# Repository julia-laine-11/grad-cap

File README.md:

# grad-cap
This is a pcb for my grad cap

## Physical:
- the pcb should cover the whole cap
- the pcb should have a space for the little tassle knob in the middle
- the battery should be flat and fit underneath the cap or pcb
- the fireworks should move while the power is on

### LED Sequence:

This was previously 16 frames, but I reduced it to 8 due to the crazy amount of traces needed (and the large amount of time to animate it). I also limited each LED to 2 frames at maximum and reduced the amount of LEDs per firework.
8 frames should be easier to route and less expensive for me to manufacture, lol

### Hardware
- While I originally planned to use a 555 timer, the MIP557 is made to be used in astable mode so I will use that
- It will have a potentiometer instead of a static resistor so that the frame rate can be sped up/lowered

- I did add a footprint for a 555 on the back in case I cannot get this chip to work. I do not have one in person to prototype with.

- the pulse will go into a binary incrementer. At first I was going to use make it myself with 3 flip flops but I couldn't find the chips I needed at the ECE shop so I will just use a binary incrementer that is available.

- the output of the incrementer is then demuxed 3:8

- the demuxed output then goes to OR gates for sections that are active for multiple frames

- and then the rest of the outputs from the mux and the outputs from the OR gates are sent to the MOSFETs

- the LEDs are color coded to what section they are a part of.
- from vote of my friends and family, the stems of the fireworks are white while the blooms are different color.

LED resistors:
- input: 3.7v  

  - white: 3.1v  20mA
  
    - 3.7-3.1 = .6/.02 = 30

  - amber: 2v 20mA
  
    - 3.7-2 = 1.7/.02 = 85

  - red: 2v 20mA
  
    - 3.7-2 = 1.7/.02 = 85

  - green: 2.2v 20mA
  
    - 3.7-2.2 = 1.5/.02 = 75
   
30 ohms: 16

80 ohms: 51

#### Prototyping
- I used the 3v output from my STM proto board to power it. The battery will output 3.7v but all of the datasheets say the components can use 3.7v so it's fine.
- I was having difficulty with the output (the gif is short, but yes this is the output)

- This was frustrating since the outputs from the incrementor were displaying properly. (from top to bottom- clock, A0, A1, A2)

- turns out I had the outputs mismatched. I had the input to the mux (A1 and A0) swapped.

- here it is working (going counting in order - 1 is at the top)

- I also needed to check my sizing now that I actually have my cap. I got the initial measurements from a friend who already graduated

- Square width: 23.5 cm
- Button diameter: 2.36 cm

    - I will make the overall board a little less than the square width, and the hole for the button a little larger.

- initial kicad measurements from my friend:

- Rectangle: 24cm, button: 26cm
- rectangle needs to shrink, button is fine :)

- final shape:

#### PCB Images 😀
- I am still working on the silkscreen

- the purdue emblem is on the solder mask layer so it is copper colored
- the handwriting is in silkscreen

- The trace widths for the main branches are 22mils. there are a maximum of ~8 LEDs per branch so I used the digikey trace width calculator and found this width is fine. there are no internal layers so I didnt need to make it any wider.
- power traces are 40 mils.

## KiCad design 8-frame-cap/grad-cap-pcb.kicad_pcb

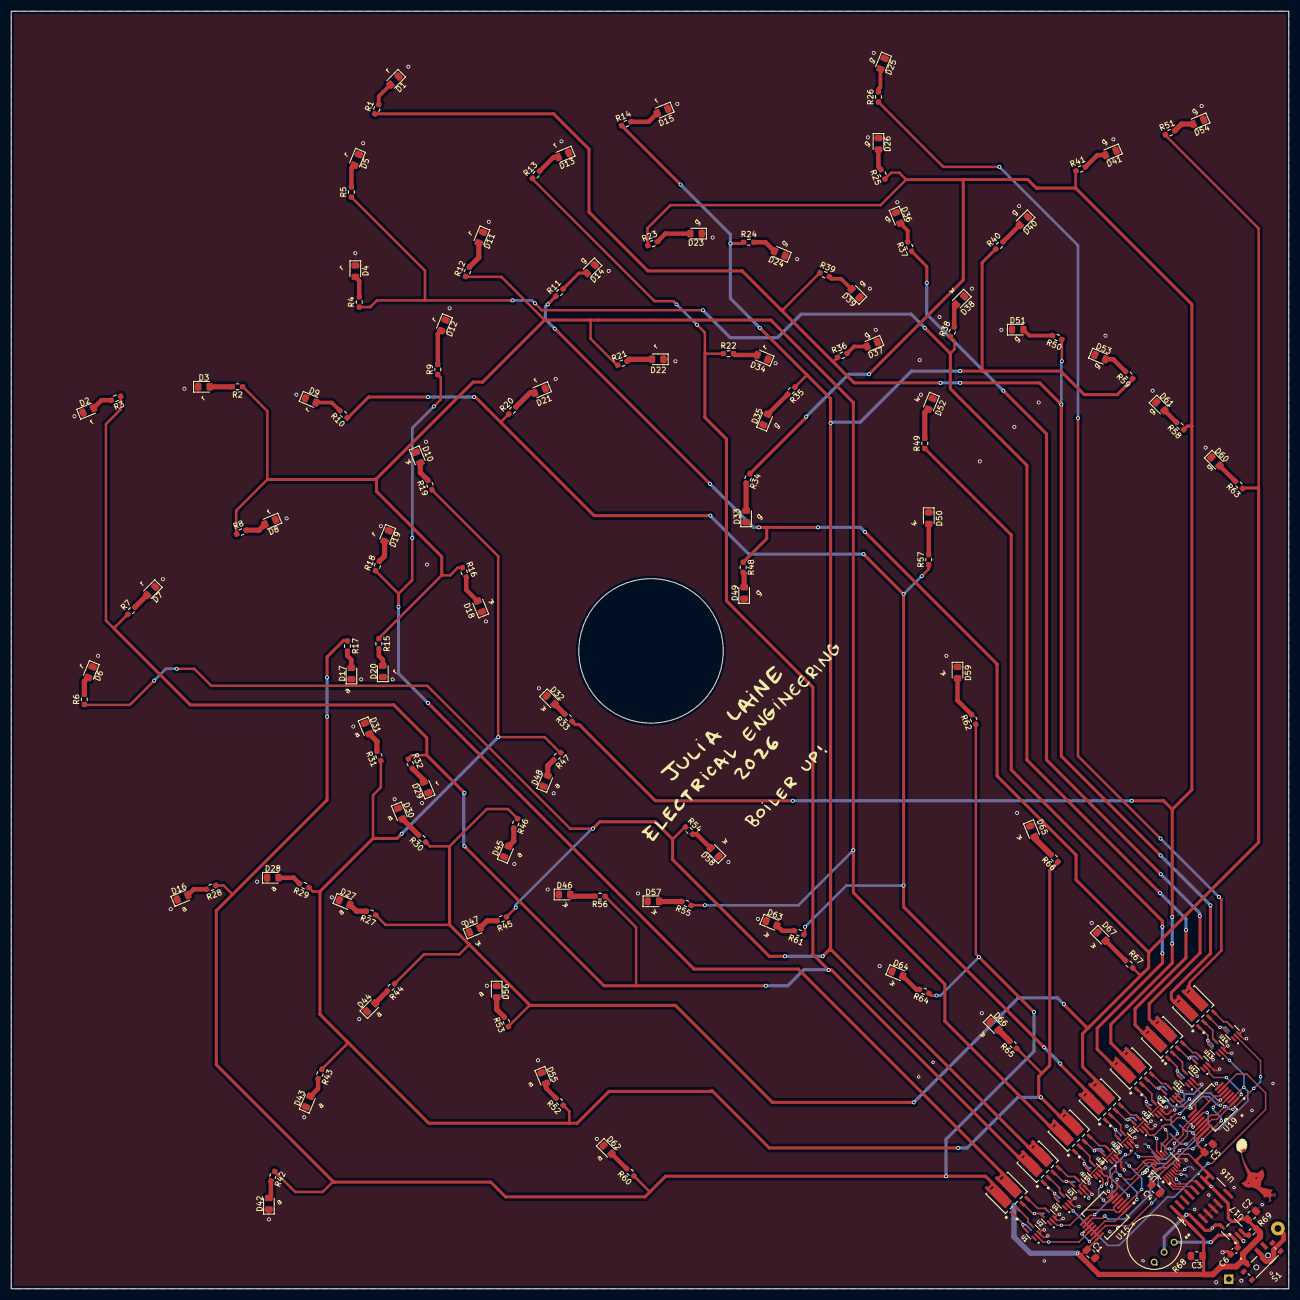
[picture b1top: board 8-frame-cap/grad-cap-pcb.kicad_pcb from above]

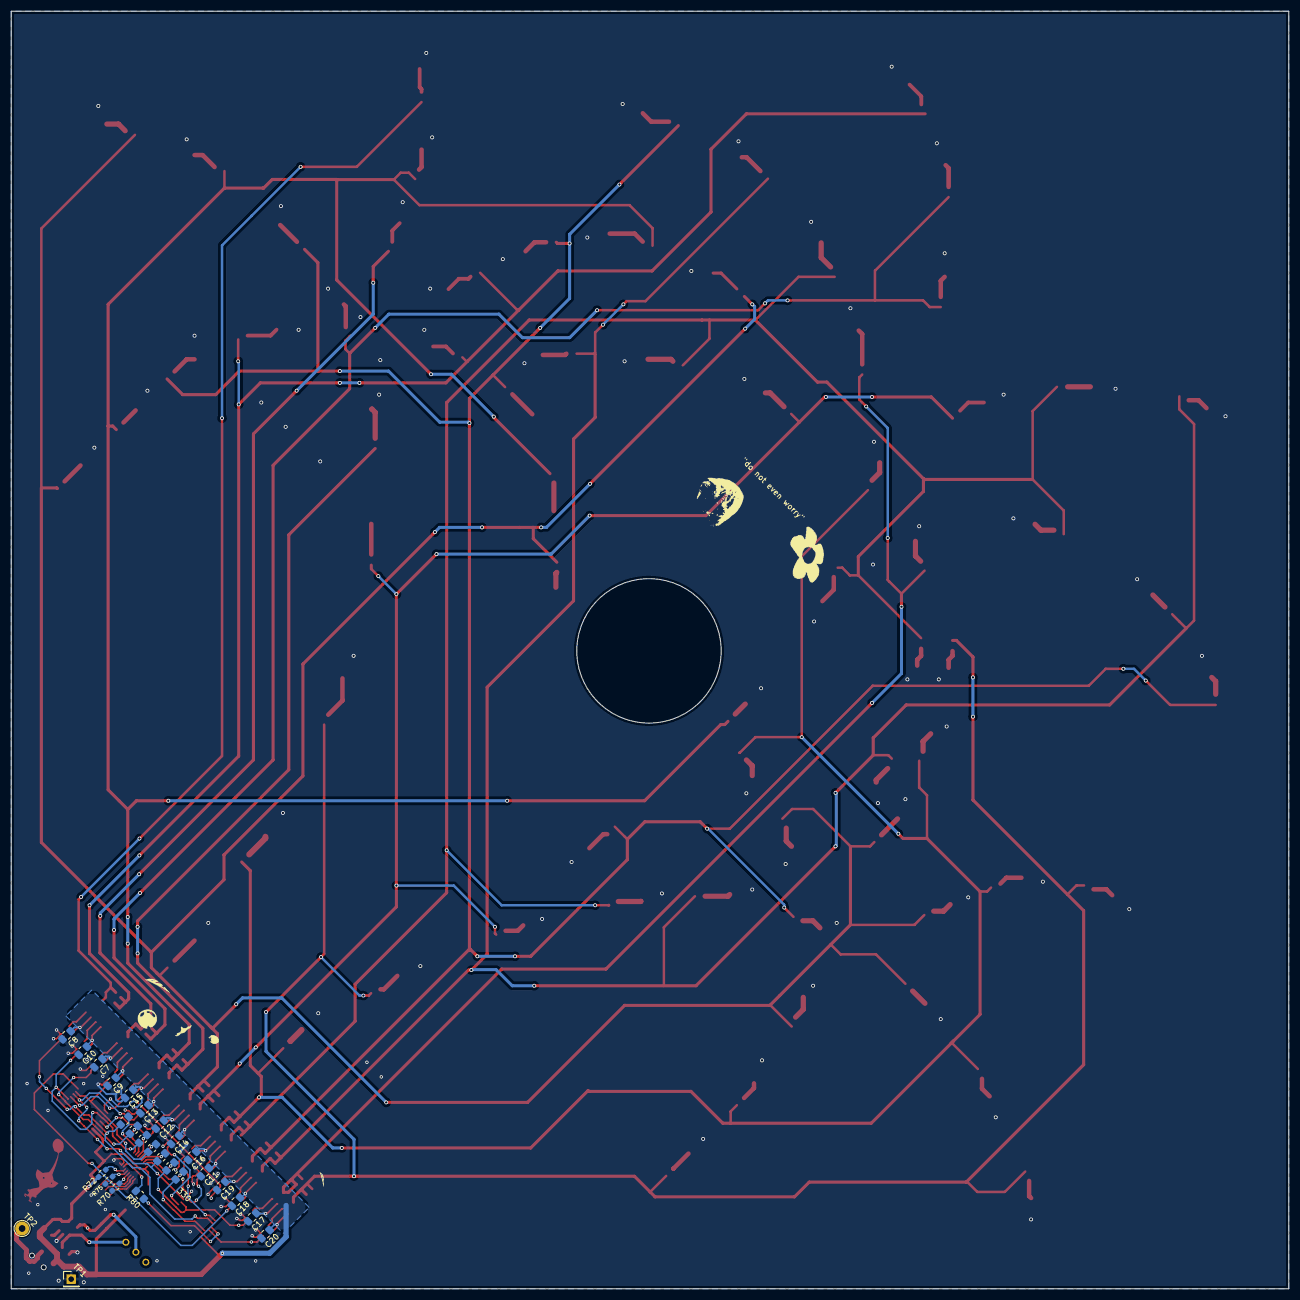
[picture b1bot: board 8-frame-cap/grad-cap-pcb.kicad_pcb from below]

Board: 2 copper layers, 230.0 x 230.0 mm, 196 parts (27 on the bottom side), 131 nets.

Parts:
C1, C2, C3, C4, C5, C7, C8, C9, C10, C11, C12, C13, C14, C15, C16, C17, C18, C19, C20: .1uf; C_0805_2012Metric_Pad1.18x1.45mm_HandSolder
C6: .1uF; C_0603_1608Metric_Pad1.08x0.95mm_HandSolder
D1, D2, D3, D4, D5, D6, D7, D8, D9, D10, D11, D12, D13, D14, D15, D16, D17, D18, D19, D20, D21, D22, D23, D24, D25, D26, D27, D28, D29, D30, D31, D32, D33, D34, D35, D36, D37, D38, D39, D40, D41, D42, D43, D44, D45, D46, D47, D48, D49, D50, D51, D52, D53, D54, D55, D56, D57, D58, D59, D60, D61, D62, D63, D64, D65, D66, D67: LED_0805_2012Metric_Pad1.15x1.40mm_HandSolder
R1, R2, R3, R4, R5, R6, R7, R8, R9, R10, R11, R12, R13, R14, R15, R16, R17, R18, R19, R20, R21, R22, R23, R24, R25, R26, R27, R28, R29, R30, R31, R32, R33, R34, R35, R36, R37, R38, R39, R40, R41, R42, R43, R44, R45, R46, R47, R48, R49, R50, R51, R52, R53, R54, R55, R56, R57, R58, R59, R60, R61, R62, R63, R64, R65, R66, R67: R_Small_US; R_0603_1608Metric_Pad0.98x0.95mm_HandSolder
R68: 91AR1MEGLF; 1M-potentiometer
R69: 1M; R_0603_1608Metric_Pad0.98x0.95mm_HandSolder
R70, R72, R75: 10k; R_0603_1608Metric_Pad0.98x0.95mm_HandSolder
R71, R73, R74, R76, R77, R78, R79, R80: 300; R_0805_2012Metric_Pad1.20x1.40mm_HandSolder
S1: ON/OFF; spdt-switch
T1, T2, T3, T4, T5, T6, T7: PHPT610035PKX; PHPT610035PKX_TRANS-2PNP-100V-3A
TP1: TestPoint; PinHeader_1x01_P2.54mm_Vertical
TP2: TestPoint; TestPoint_THTPad_D2.5mm_Drill1.2mm
U1, U2, U3, U4, U5, U6, U7, U8, U9, U10, U11, U12, U13, U14: SN74LVC1G14DCKR; SN74LVC-INVERTER
U15, U19: SN74AHCT32DBR; SN74AHCT32DBR_2-INPUT-QUAD-OR
U16: SN74HC163DR; binary counter - 74hc163
U17: MIC1557YM5-TR; MIC1557
U18: SN74HCS238DYYR; SN74HCS238DYYR-3-8-MUX

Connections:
0: R78.2, U15.1 (1A), U15.12 (4A)
1: R73.2, U2.2 (A), U15.2 (1B), U15.4 (2A)
1or2: R10.1, R20.1, R57.1, R61.1, T5.8 (COLLECTOR)
2: R74.2, U5.2 (A), U15.5 (2B), U19.4 (2A)
2or3: R2.1, R8.1, R12.1, R15.1, R16.1, R21.1, R55.1, T3.8 (COLLECTOR)
3: R79.2, U11.2 (A), U19.5 (2B), U19.9 (3A)
3or4: R3.1, R7.1, R13.1, R22.1, R32.1, R56.1, T2.8 (COLLECTOR)
4: R77.2, U13.2 (A), U19.2 (1B), U19.10 (3B)
4or5: R6.1, R14.1, R24.1, R35.1, R40.1, R45.1, R54.1, R59.1, T2.6 (COLLECTOR)
5: R76.2, U12.2 (A), U19.1 (1A), U19.13 (4B)
5or6: R23.1, R25.1, R33.1, R34.1, R41.1, R58.1, T4.6 (COLLECTOR)
6: R71.2, U14.2 (A), U15.9 (3A), U19.12 (4A)
6or7: R11.1, R27.1, R30.1, R44.1, R46.1, R48.1, R51.1, R53.1, R63.1, R67.1, T5.6 (COLLECTOR)
7: R80.1, U15.10 (3B), U15.13 (4B)
7or8: R19.1, R29.1, R31.1, R43.1, R47.1, R52.1, R65.1, R66.1, T3.6 (COLLECTOR)
8or1: R17.1, R28.1, R42.1, R60.1, R62.1, R64.1, T1.8 (COLLECTOR)
557-PULSE: R68.2, U16.2 (CLK), U17.5 (OUT)
+3.3V: C1.1, C2.1, C3.1, C4.1, C5.1, C7.1, C8.1, C9.1, C10.1, C11.1, C12.1, C13.1, C14.1, C15.1, C16.1, C17.1, C18.1, C19.1, C20.1, R69.1, R72.2, S1.1, T1.1 (EMITTER), T1.3 (EMITTER), T2.1 (EMITTER), T2.3 (EMITTER), T3.1 (EMITTER), T3.3 (EMITTER), T4.1 (EMITTER), T4.3 (EMITTER), T5.1 (EMITTER), T5.3 (EMITTER), T6.1 (EMITTER), T6.3 (EMITTER), T7.1 (EMITTER), T7.3 (EMITTER), U1.5 (VCC), U2.5 (VCC), U3.5 (VCC), U4.5 (VCC), U5.5 (VCC), U6.5 (VCC), U7.5 (VCC), U8.5 (VCC), U9.5 (VCC), U10.5 (VCC), U11.5 (VCC), U12.5 (VCC), U13.5 (VCC), U14.5 (VCC), U15.14 (VCC), U16.1 (*CLR), U16.7 (ENP), U16.9 (*LOAD), U16.10 (ENT), U16.16 (VCC), U17.4 (VS), U18.16 (VCC), U19.14 (VCC)
+BATT: S1.2, TP2.1
/pd-mux-g0: R70.1, U18.4 (*G0)
/pd-mux-g1: R75.1, U18.5 (*G1)
/pu-mux-g2: R72.1, U18.6 (G2)
CLOCK1: U16.13 (QB), U18.1 (A0)
CLOCK2: U16.12 (QC), U18.2 (A1)
CLOCK3: U16.11 (QD), U18.3 (A2)
GND: C1.2, C2.2, C3.2, C4.2, C5.2, C6.2, C7.2, C8.2, C9.2, C10.2, C11.2, C12.2, C13.2, C14.2, C15.2, C16.2, C17.2, C18.2, C19.2, C20.2, D1.1 (K), D2.1 (K), D3.1 (K), D4.1 (K), D5.1 (K), D6.1 (K), D7.1 (K), D8.1 (K), D9.1 (K), D10.1 (K), D11.1 (K), D12.1 (K), D13.1 (K), D14.1 (K), D15.1 (K), D16.1 (K), D17.1 (K), D18.1 (K), D19.1 (K), D20.1 (K), D21.1 (K), D22.1 (K), D23.1 (K), D24.1 (K), D25.1 (K), D26.1 (K), D27.1 (K), D28.1 (K), D29.1 (K), D30.1 (K), D31.1 (K), D32.1 (K), D33.1 (K), D34.1 (K), D35.1 (K), D36.1 (K), D37.1 (K), D38.1 (K), D39.1 (K), D40.1 (K), D41.1 (K), D42.1 (K), D43.1 (K), D44.1 (K), D45.1 (K), D46.1 (K), D47.1 (K), D48.1 (K), D49.1 (K), D50.1 (K), D51.1 (K), D52.1 (K), D53.1 (K), D54.1 (K), D55.1 (K), D56.1 (K), D57.1 (K), D58.1 (K), D59.1 (K), D60.1 (K), D61.1 (K), D62.1 (K), D63.1 (K), D64.1 (K), D65.1 (K), D66.1 (K), D67.1 (K), R70.2, R75.2, S1.3, TP1.1, U1.3 (GND), U2.3 (GND), U3.3 (GND), U4.3 (GND), U5.3 (GND), U6.3 (GND), U7.3 (GND), U8.3 (GND), U9.3 (GND), U10.3 (GND), U11.3 (GND), U12.3 (GND), U13.3 (GND), U14.3 (GND), U15.7 (GND), U16.3 (A), U16.4 (B), U16.5 (C), U16.6 (D), U16.8 (GND), U17.2 (GND), U18.8 (GND), U19.7 (GND)
unnamed: D66.2 (A), R65.2
unnamed: D64.2 (A), R64.2
unnamed: D63.2 (A), R61.2
unnamed: D57.2 (A), R55.2
unnamed: D46.2 (A), R56.2
unnamed: D47.2 (A), R45.2
unnamed: D56.2 (A), R53.2
unnamed: D55.2 (A), R52.2
unnamed: D62.2 (A), R60.2
unnamed: D44.2 (A), R44.2
unnamed: D43.2 (A), R43.2
unnamed: D42.2 (A), R42.2
unnamed: D27.2 (A), R27.2
unnamed: D28.2 (A), R29.2
unnamed: D16.2 (A), R28.2
unnamed: D30.2 (A), R30.2
unnamed: D31.2 (A), R31.2
unnamed: D17.2 (A), R17.2
unnamed: D45.2 (A), R46.2
unnamed: D48.2 (A), R47.2
unnamed: D58.2 (A), R54.2
unnamed: D32.2 (A), R33.2
unnamed: D18.2 (A), R16.2
unnamed: D10.2 (A), R19.2
unnamed: D19.2 (A), R18.2
unnamed: D20.2 (A), R15.2
unnamed: D29.2 (A), R32.2
unnamed: D8.2 (A), R8.2
unnamed: D7.2 (A), R7.2
unnamed: D6.2 (A), R6.2
unnamed: D9.2 (A), R10.2
unnamed: D3.2 (A), R2.2
unnamed: D2.2 (A), R3.2
unnamed: D4.2 (A), R4.2
unnamed: D5.2 (A), R5.2
unnamed: D1.2 (A), R1.2
unnamed: D12.2 (A), R9.2
unnamed: D11.2 (A), R12.2
unnamed: D13.2 (A), R13.2
unnamed: D15.2 (A), R14.2
unnamed: D21.2 (A), R20.2
unnamed: D22.2 (A), R21.2
unnamed: D34.2 (A), R22.2
unnamed: D67.2 (A), R67.2
unnamed: D65.2 (A), R66.2
unnamed: D59.2 (A), R62.2
unnamed: D50.2 (A), R57.2
unnamed: D52.2 (A), R49.2
unnamed: D38.2 (A), R38.2
unnamed: D37.2 (A), R36.2
unnamed: D35.2 (A), R35.2
unnamed: D33.2 (A), R34.2
unnamed: D49.2 (A), R48.2
unnamed: D39.2 (A), R39.2
unnamed: D24.2 (A), R24.2
unnamed: D23.2 (A), R23.2
unnamed: D14.2 (A), R11.2
unnamed: D36.2 (A), R37.2
unnamed: D26.2 (A), R25.2
unnamed: D25.2 (A), R26.2
unnamed: D40.2 (A), R40.2
unnamed: D41.2 (A), R41.2
unnamed: D54.2 (A), R51.2
unnamed: D51.2 (A), R50.2
unnamed: D53.2 (A), R59.2
unnamed: D61.2 (A), R58.2
unnamed: D60.2 (A), R63.2
unnamed: R69.2, U17.3 (CS)
unnamed: C6.1, R68.3, U17.1 (T/T)
unnamed: R78.1, U18.15 (Y0)
unnamed: R73.1, U18.14 (Y1)
unnamed: R74.1, U18.13 (Y2)
unnamed: R79.1, U18.12 (Y3)
unnamed: R77.1, U18.11 (Y4)
unnamed: R76.1, U18.10 (Y5)
unnamed: R71.1, U18.9 (Y6)
unnamed: R80.2, U18.7 (Y7)
unnamed: T1.2 (BASE), U1.4 (Y)
unnamed: T3.2 (BASE), U10.4 (Y)
unnamed: T4.2 (BASE), U5.4 (Y)
unnamed: T7.2 (BASE), U13.4 (Y)
unnamed: T1.4 (BASE), U2.4 (Y)
unnamed: T3.4 (BASE), U8.4 (Y)
unnamed: T4.4 (BASE), U6.4 (Y)
unnamed: T7.4 (BASE), U14.4 (Y)
unnamed: T2.2 (BASE), U4.4 (Y)
unnamed: T5.2 (BASE), U9.4 (Y)
unnamed: T6.2 (BASE), U11.4 (Y)
unnamed: T2.4 (BASE), U3.4 (Y)
unnamed: T5.4 (BASE), U7.4 (Y)
unnamed: T6.4 (BASE), U12.4 (Y)
f1or2: U9.2 (A), U15.3 (1Y)
f1or8: U1.2 (A), U15.11 (4Y)
f2or3: U10.2 (A), U15.6 (2Y)
f3or4: U4.2 (A), U19.6 (2Y)
f4or5: U3.2 (A), U19.8 (3Y)
f5or6: U6.2 (A), U19.3 (1Y)
f6or7: U7.2 (A), U19.11 (4Y)
f7or8: U8.2 (A), U15.8 (3Y)
frame1: R9.1, R18.1, T1.6 (COLLECTOR)
frame2: R49.1, T4.8 (COLLECTOR)
frame3: R4.1, R5.1, R38.1, T6.8 (COLLECTOR)
frame4: R1.1, R36.1, R39.1, R50.1, T7.8 (COLLECTOR)
frame5: R37.1, T6.6 (COLLECTOR)
frame6: R26.1, T7.6 (COLLECTOR)

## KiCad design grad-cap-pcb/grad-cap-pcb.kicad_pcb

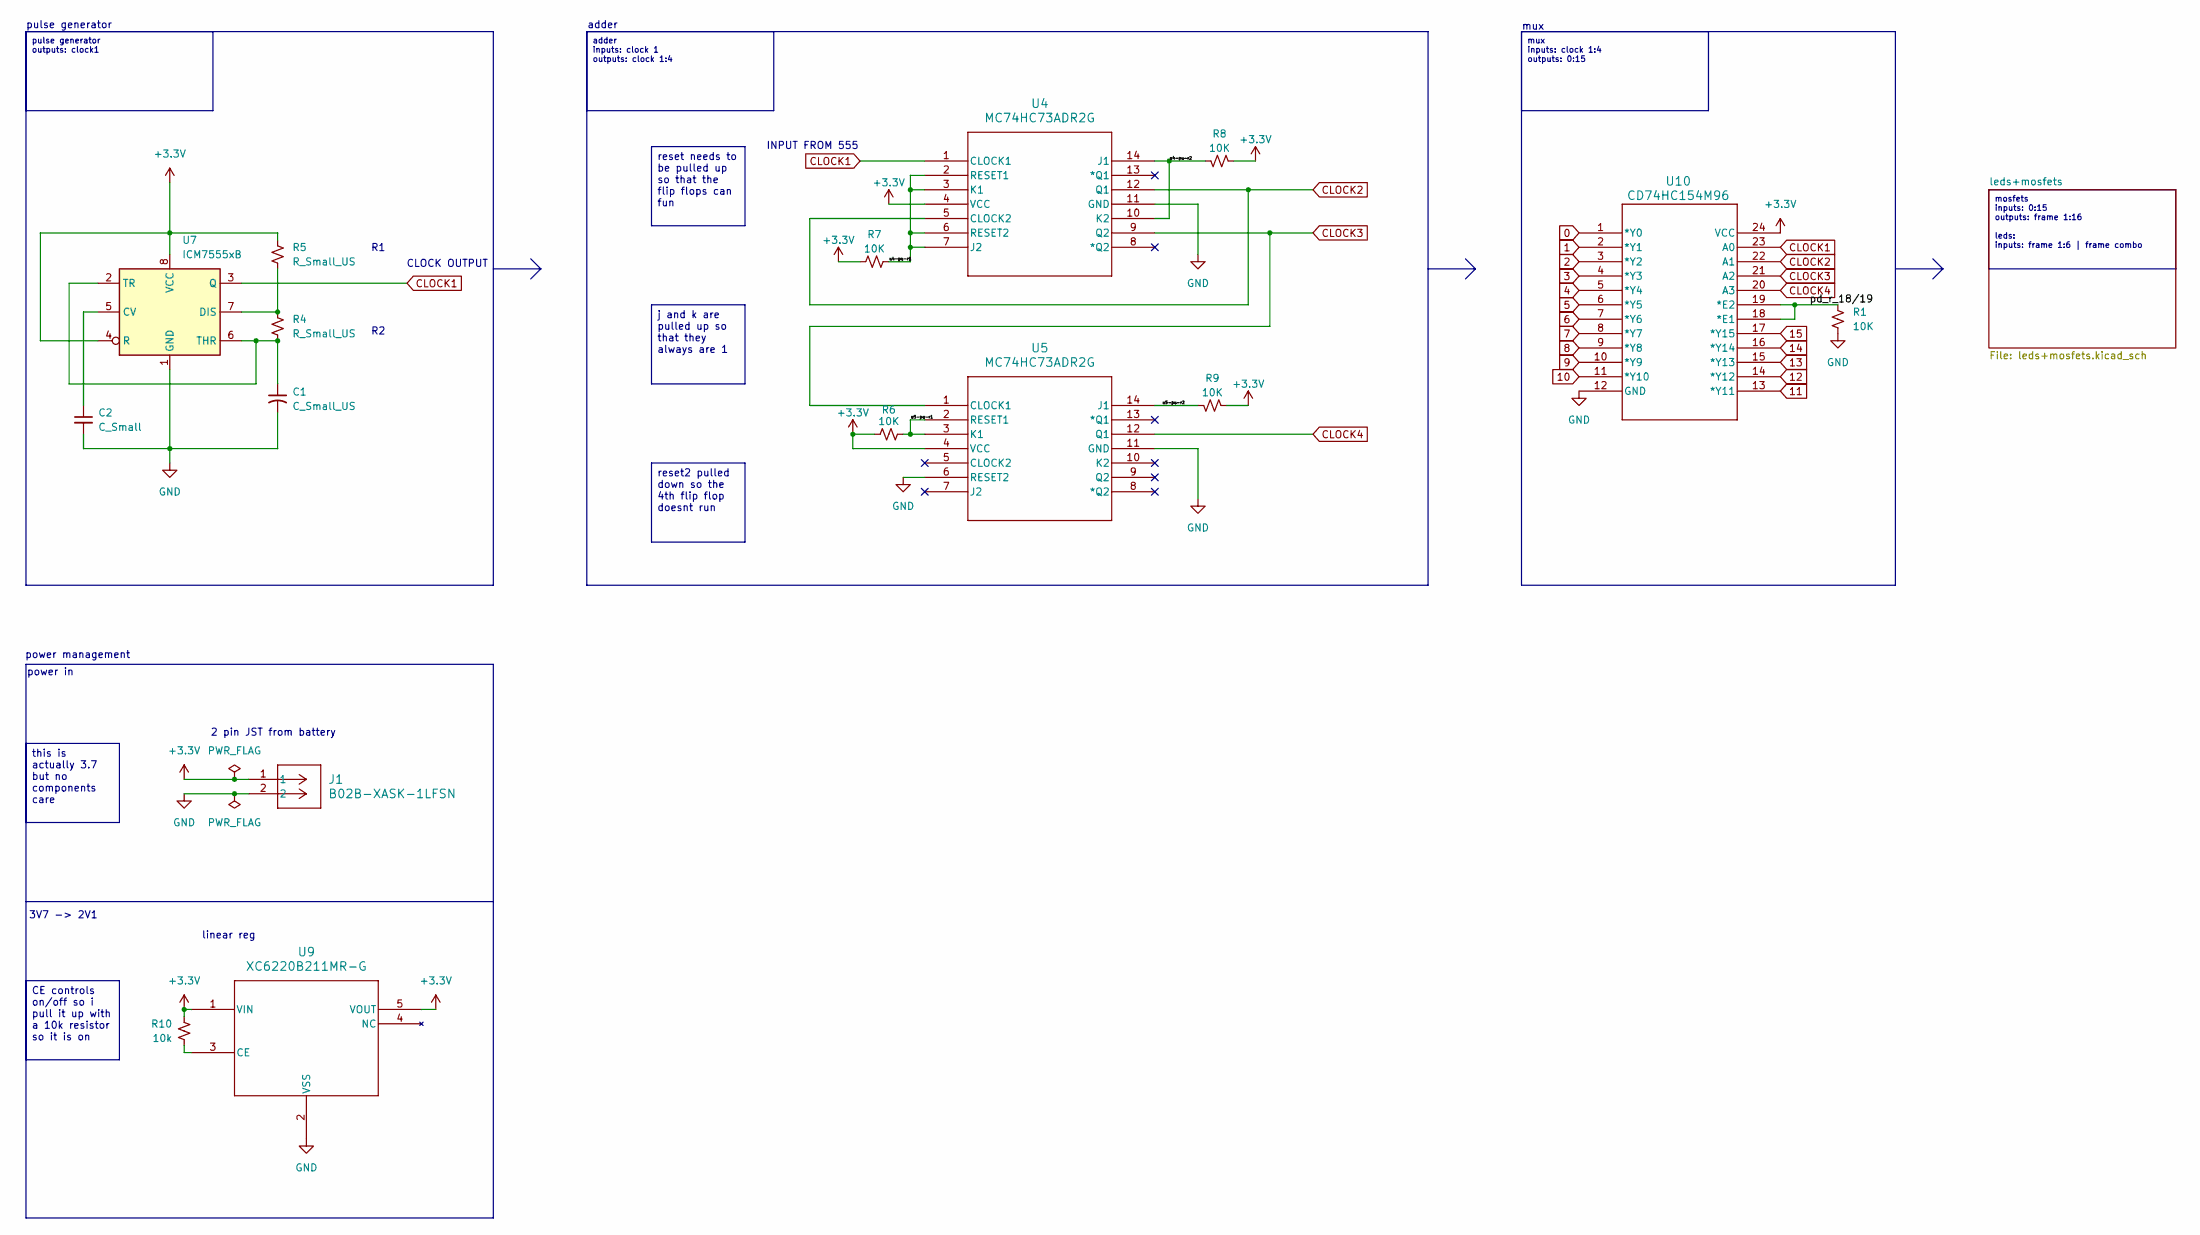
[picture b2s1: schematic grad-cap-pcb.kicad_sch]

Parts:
C1: C_Small_US; C_0805_2012Metric_Pad1.18x1.45mm_HandSolder
C2: C_Small; C_0805_2012Metric_Pad1.18x1.45mm_HandSolder
J1: B02B-XASK-1LFSN; 1X02JST
R1, R6, R7, R8, R9: 10K; R_0805_2012Metric_Pad1.20x1.40mm_HandSolder
R4, R5: R_Small_US; R_0805_2012Metric_Pad1.20x1.40mm_HandSolder
R10: 10k; R_0805_2012Metric_Pad1.20x1.40mm_HandSolder
U4, U5: MC74HC73ADR2G; MC74HC73ADR2G_JK-FLIPFLOP
U7: ICM7555xB; SOIC-8_3.9x4.9mm_P1.27mm
U9: XC6220B211MR-G; XC6220B21MR_2.1V-1A-REG
U10: CD74HC154M96; CD74HC154M96_4-16-MUX

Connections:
0: U10.1 (*Y0); also elsewhere on the board
1: U10.2 (*Y1); also elsewhere on the board
2: U10.3 (*Y2); also elsewhere on the board
3: U10.4 (*Y3); also elsewhere on the board
4: U10.5 (*Y4); also elsewhere on the board
5: U10.6 (*Y5); also elsewhere on the board
6: U10.7 (*Y6); also elsewhere on the board
7: U10.8 (*Y7); also elsewhere on the board
8: U10.9 (*Y8); also elsewhere on the board
9: U10.10 (*Y9); also elsewhere on the board
10: U10.11 (*Y10); also elsewhere on the board
11: U10.13 (*Y11); also elsewhere on the board
12: U10.14 (*Y12); also elsewhere on the board
13: U10.15 (*Y13); also elsewhere on the board
14: U10.16 (*Y14); also elsewhere on the board
15: U10.17 (*Y15); also elsewhere on the board
+3.3V: J1.1, R5.1, R6.1, R7.1, R8.1, R9.1, R10.1, U4.4 (VCC), U5.4 (VCC), U7.4 (R), U7.8 (VCC), U9.1 (VIN), U9.5 (VOUT), U10.24 (VCC); also elsewhere on the board
/pd_r_18/19: R1.1, U10.18 (*E1), U10.19 (*E2)
/u4-pu-r1: R7.2, U4.2 (RESET1), U4.3 (K1), U4.6 (RESET2), U4.7 (J2)
/u4-pu-r2: R8.2, U4.10 (K2), U4.14 (J1)
/u5-pu-r1: R6.2, U5.2 (RESET1), U5.3 (K1)
/u5-pu-r2: R9.2, U5.14 (J1)
CLOCK1: U4.1 (CLOCK1), U7.3 (Q), U10.23 (A0)
CLOCK2: U4.5 (CLOCK2), U4.12 (Q1), U10.22 (A1)
CLOCK3: U4.9 (Q2), U5.1 (CLOCK1), U10.21 (A2)
CLOCK4: U5.12 (Q1), U10.20 (A3)
GND: C1.2, C2.2, J1.2, R1.2, U4.11 (GND), U5.6 (RESET2), U5.11 (GND), U7.1 (GND), U9.2 (VSS), U10.12 (GND); also elsewhere on the board
unnamed: C2.1, U7.5 (CV)
unnamed: R4.1, R5.2, U7.7 (DIS)
unnamed: C1.1, R4.2, U7.2 (TR), U7.6 (THR)
unnamed: R10.2, U9.3 (CE)

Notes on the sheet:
CLOCK OUTPUT
INPUT FROM 555
adder
3V7 -> 2V1
mux
linear reg
pulse generator
power management
2 pin JST from battery
power in
j and k are pulled up so that they always are 1
reset2 pulled down so the 4th flip flop doesnt run
mosfets inputs: 0:15 outputs: frame 1:16 leds: inputs: frame 1:6 | frame combo
reset needs to be pulled up so that the flip flops can fun
CE controls on/off so i pull it up with a 10k resistor so it is on
pulse generator outputs: clock1
mux inputs: clock 1:4 outputs: 0:15
adder inputs: clock 1 outputs: clock 1:4
this is actually 3.7 but no components care
